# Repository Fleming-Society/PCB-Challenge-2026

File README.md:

# UCL x KCL x Oxford x Imperial x Cambridge x Edinburgh: 2026 PCB Challenge | Sponsored by PCBWay and Jane Street

UCL, KCL and Oxford, Cambridge, Imperial and Edinburgh are proud to present the 2026 PCB Challenge. Many thanks to PCBWay and Jane Street for sponsoring the prizes. 

<p align="center">
  <a href="https://www.janestreet.com">
    <picture>
      <source media="(prefers-color-scheme: dark)" srcset="assets/sponsors/janestreet.png">
      
    </picture>
  </a>
  &nbsp;&nbsp;&nbsp;&nbsp;&nbsp;&nbsp;
  
</p>

If you have any questions please email zceepvb@ucl.ac.uk. Please keep in mind you cannot make a submission/be eligible for the prizes if you do not attend any of the universities organising this event. Within the 7 day period this event is being hosted, any university Engineering society is free to reach out to collaborate at this email address. 

All files are meant for KiCAD v10.0, if you have not updated, you probably should. It is a much better version than KiCAD v9.0 (includes dark mode). 

The event is running from the **12th of October to the 19th of October.**

## Overview

This challenge invites participants to implement the given schematic as a fully wired PCB in the smallest possible size. As an added challenge the purpose of the PCB itself is left ambiguous. You are provided a schematic with all component values and connections intact, and a footprint associated with each schematic symbol. The event runs fully online, and all the necessary information can be found in this GitHub. 

I was inspired to create this challenge by a friend, Taylan Arslan, who gave me what was an essentially impossible challenge to get his PCB to fit within a 40mmx40mm constraint. Despite it being impossible, I learned a lot in those two days trying to accomplish this and the end result is a PCB that I am still very proud of. I hope that participants will also share the same feeling of satisfaction that I got, with the added bonus that this one is not impossible since the smallest possible size is to be determined by one of you. 

From my own experience, no matter how much you may like designing PCBs, ultimately it will become a bit repetitive. Thus to make this challenge more interesting; besides the monetary prize; I also decided to make the purpose of the PCB itself a puzzle to be solved.

## The Challenge

1. **Logic Deduction**: deduce the digital logic function implemented by the provided schematic, purely from the schematic itself (no functional description is given). Deducing this will give you bonus points.
2. **PCB Layout**: design a fully wired, single board PCB implementation of that logic, optimised for the smallest possible board area, within the design constraints below.

This challenge will be running for 7 days, **until the midnight of October 19th. (The end of the 19th)**

Make your **submission** here:
https://forms.cloud.microsoft/Pages/ResponsePage.aspx?id=_oivH5ipW0yTySEKEdmlwtUrHdFLQS5OlbEozvc0DnlUMzJQWkFZVDhVRjZNVTlCQjhHQ0hDSUxSQi4u

Your challenge submission should be a public GitHub repo. In this repo you just need to include the files we need. Your submission for the logic deduction is in the form itself. 

## Design Constraints

The keep out zone of the ESP32 antenna does not have to cover any PCB area, it can be left hanging off the edge of the PCB. Furthermore ignore the datasheets associated with each component in this challenge.

### Board & Layer Stack
- Four layer board (F.Cu / B.Cu + 2 inner layers), 1.6 mm standard FR4 thickness.
- Board outline may be any shape, but must be a single contiguous board (no panelisation or multi-board tricks to reduce measured area).
- Management of the 4 layer stack up (e.g. assignment of signal/power/ground to inner layers) is left entirely to the participant; there is no required or predefined ground/power/signal layer assignment. However, you will be penalised for a stack up that would not actually work. 

### Trace & Clearance Rules
- Minimum trace width: 0.15 mm (6 mil).
- Minimum clearance (trace to trace, trace to pad, trace to via): 0.12 mm (6 mil) (changed from 0.15mm to 0.12mm due to the pads of the flip flop being seperated by 0.12mm).
- Minimum copper to board edge clearance: 0.3 mm.
- These values should be set as the global minimum in KiCad's Clearance rules so DRC enforces them automatically. We will check the DRC ourselves when judging. 

### Via Rules
- Minimum via drill diameter: 0.3 mm.
- Minimum via annular ring: 0.15 mm (i.e. minimum via pad diameter of approximately 0.6 mm).
- Vias in pads are not permitted.

### Footprint Rules
- Only default KiCad footprints, or footprints explicitly provided as part of the challenge, may be used.
- Footprints must not be modified from the library originals (this will be checked via KiCad's "footprint does not match library" DRC warning; note that editing a local copy of the library will not bypass this check, and manual review may also be used).
- All footprints must have correctly defined courtyard layers (F.CrtYd / B.CrtYd), and courtyards must not overlap between components. This is enforced via KiCad's built in "courtyard overlap" DRC check.
- Traces and vias may not be routed underneath IC footprints (i.e. within the courtyard area of any IC); given there is no shield underneath it. This only applies if the IC and trace are on the same layer.

### Silkscreen
- Boards do not need to retain fully legible silkscreen labelling. 

### DRC Pass Criteria
- All submitted boards must pass KiCad's Design Rule Checker to a good degree (Inspect → Design Rules Checker). I understand that the DRC can be quite buggy especially with imported footprints, thus I will be a bit lenient. 
- DRC **warnings** (e.g. minor silkscreen clipping) will not disqualify a board, but excessive or careless warnings may count against a board at the routing quality tie break stage.

#### I am aware that there is an issue with the flip flop footprints and we will ignore any DRC errors associated with them. Just ensure you use a trace width of 0.17mm or less for them. 

### Note on High-Speed & Power Rules
The challenge schematic does include a high speed signal paths (a differential pair requiring a continuous reference plane). It does not however have a significant power delivery requirement (e.g. wide power traces, stitching vias). As such, no specific power plane rules are imposed in this iteration. 

## Judging Criteria

1. **Pass/fail gate**: correct logic deduction and a fully wired, DRC clean board (zero errors) under the given constraints. Boards failing either condition are not eligible for prizes.
2. **Primary ranking metric**: smallest board area (bounding box of the board outline), among all boards that pass the gate above.
3. **Tie breaker**: in the event of a tie, judges will assess routing quality and general layout practice (e.g. via count, trace directness, use of ground fill, silkscreen space, DRC warning count) to determine placement.

## Prizes

- **1st place:** £200
- **2nd place:** £100
- **3rd place:** £50

- **Top 10**: Jane Street Water Bottle
- **Top 65**: Jane Street Tech T-Shirt, 10$ PCBWay Coupon and a PCB Ruler

- All participants who submit a valid entry will receive a certificate of participation, a 10$ coupon on orders above 30$ for PCBWay and a PCB ruler from PCBWay. To be classified as a participant you must actually complete the PCB, this meaning that all the connections have been connected with a trace. Auto trace does not count. 

Expect the results to be announced within a week or two from the end date of the challenge.

## Sponsors

Thank you to our sponsors for making this challenge possible.

<p align="center">
  <a href="https://www.janestreet.com">
    <picture>
      <source media="(prefers-color-scheme: dark)" srcset="assets/sponsors/janestreet.png">
      
    </picture>
  </a>
  &nbsp;&nbsp;&nbsp;&nbsp;&nbsp;&nbsp;
  
</p>

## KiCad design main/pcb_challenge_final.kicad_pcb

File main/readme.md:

## Issues
1. C1-C8, R1, SW1 and SW3 did not have a footprint. 
2. The transistor did not have the correct nets due to being numbered 1, 5 and 6 rather than 1, 2 and 3. 
3. 3v3 instead of +3.3V power net. 
4. Input 1,  Input2, Input 3 and Input 4 rather than b1, b2, b3 and 4.
5. U2 is not a real component.
6. SW2 pins were both GND. This has been resolved.
7. EN on the clock generator should be en. 
8. R24 and R6 do not show a connection to S1, they are supposed to be connected. 

#### Credits to: 
Mickey Techachokwiwat, Andy Gao and Lutfi Cengiz for finding these issues and reporting them to me.

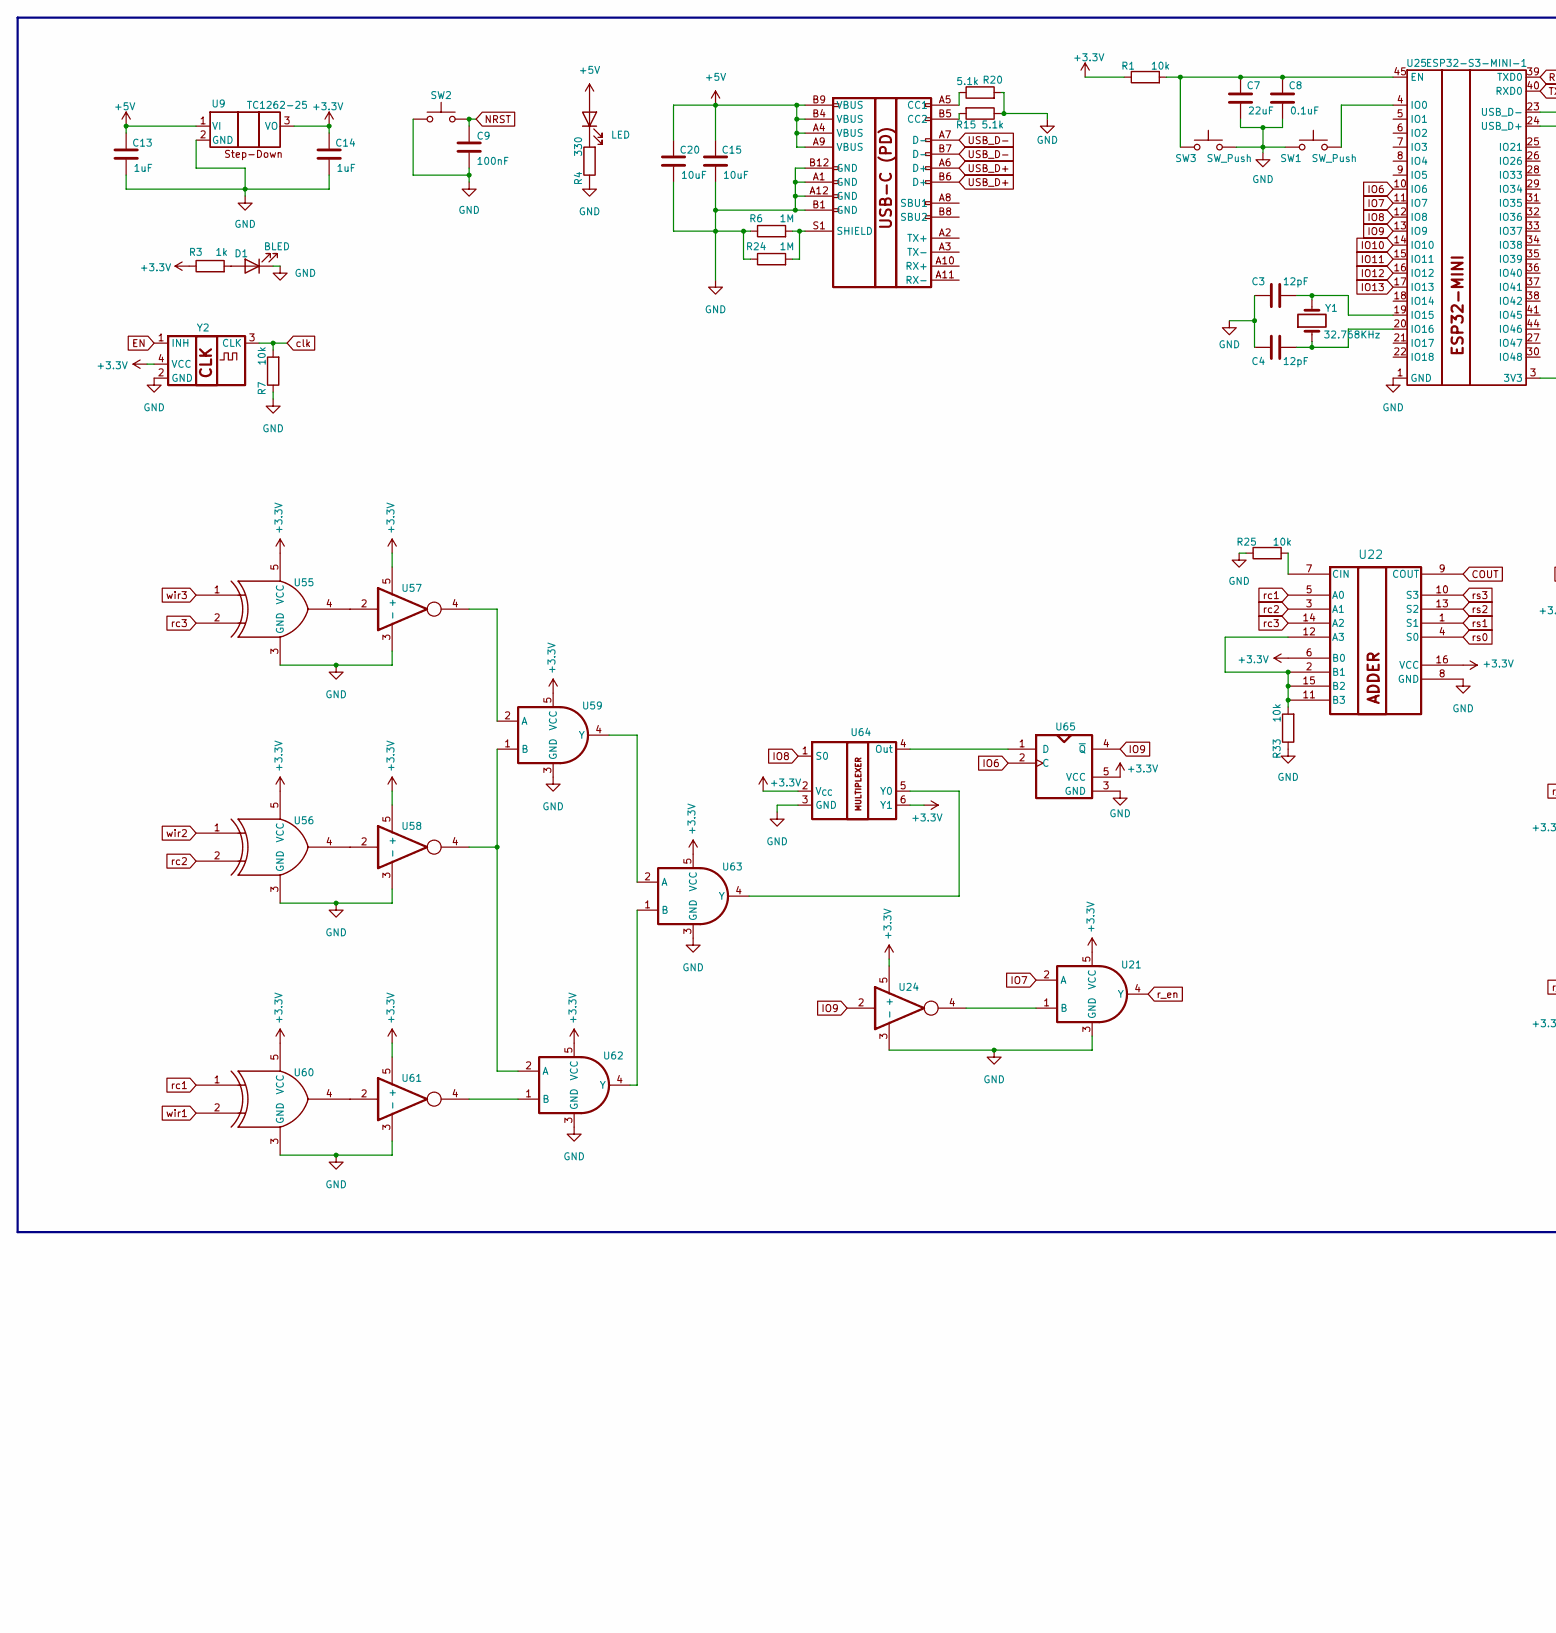
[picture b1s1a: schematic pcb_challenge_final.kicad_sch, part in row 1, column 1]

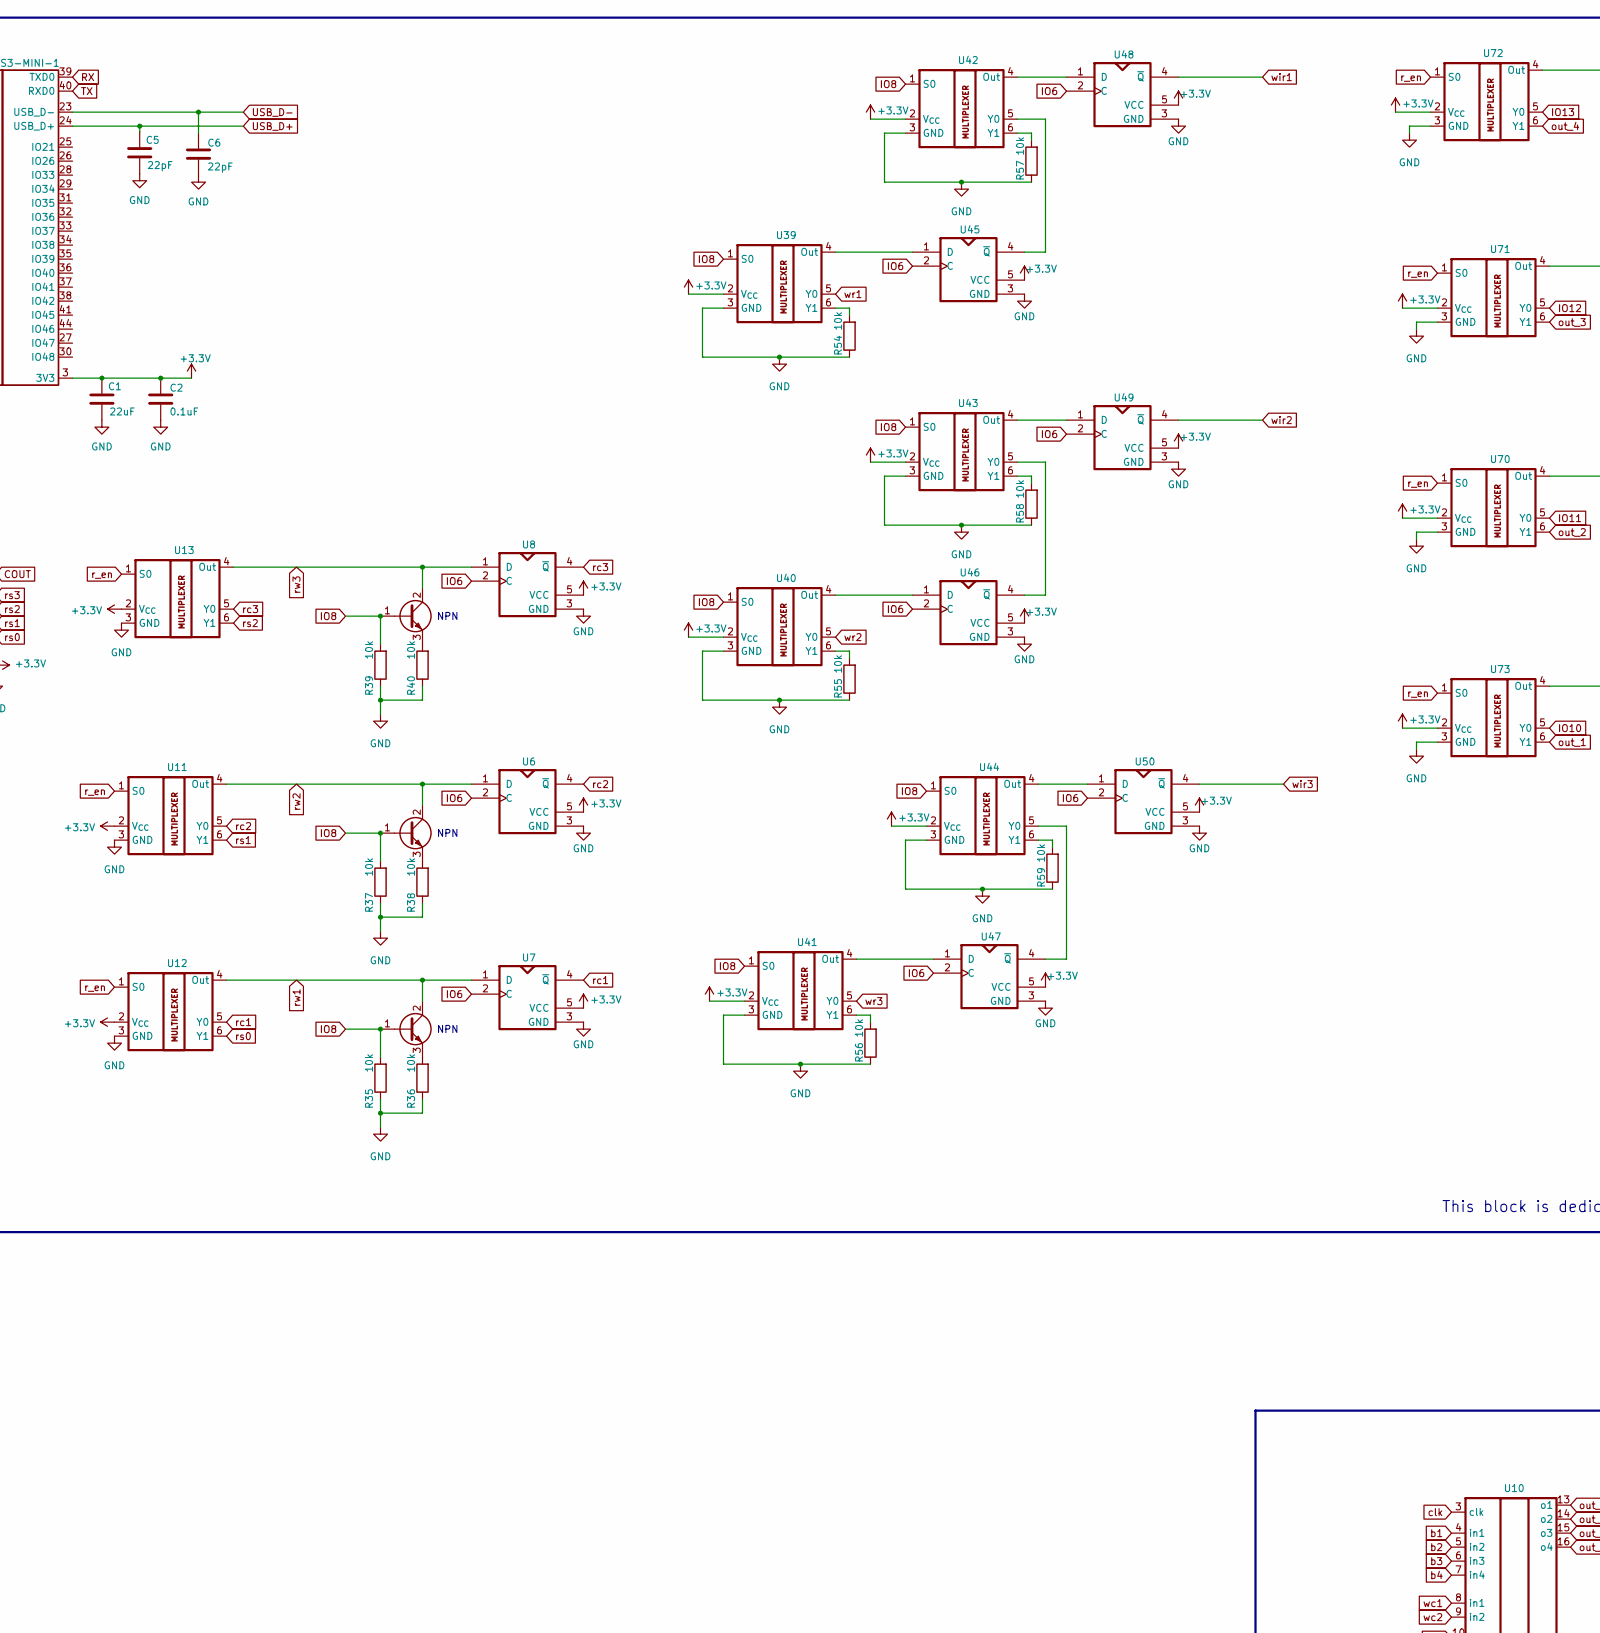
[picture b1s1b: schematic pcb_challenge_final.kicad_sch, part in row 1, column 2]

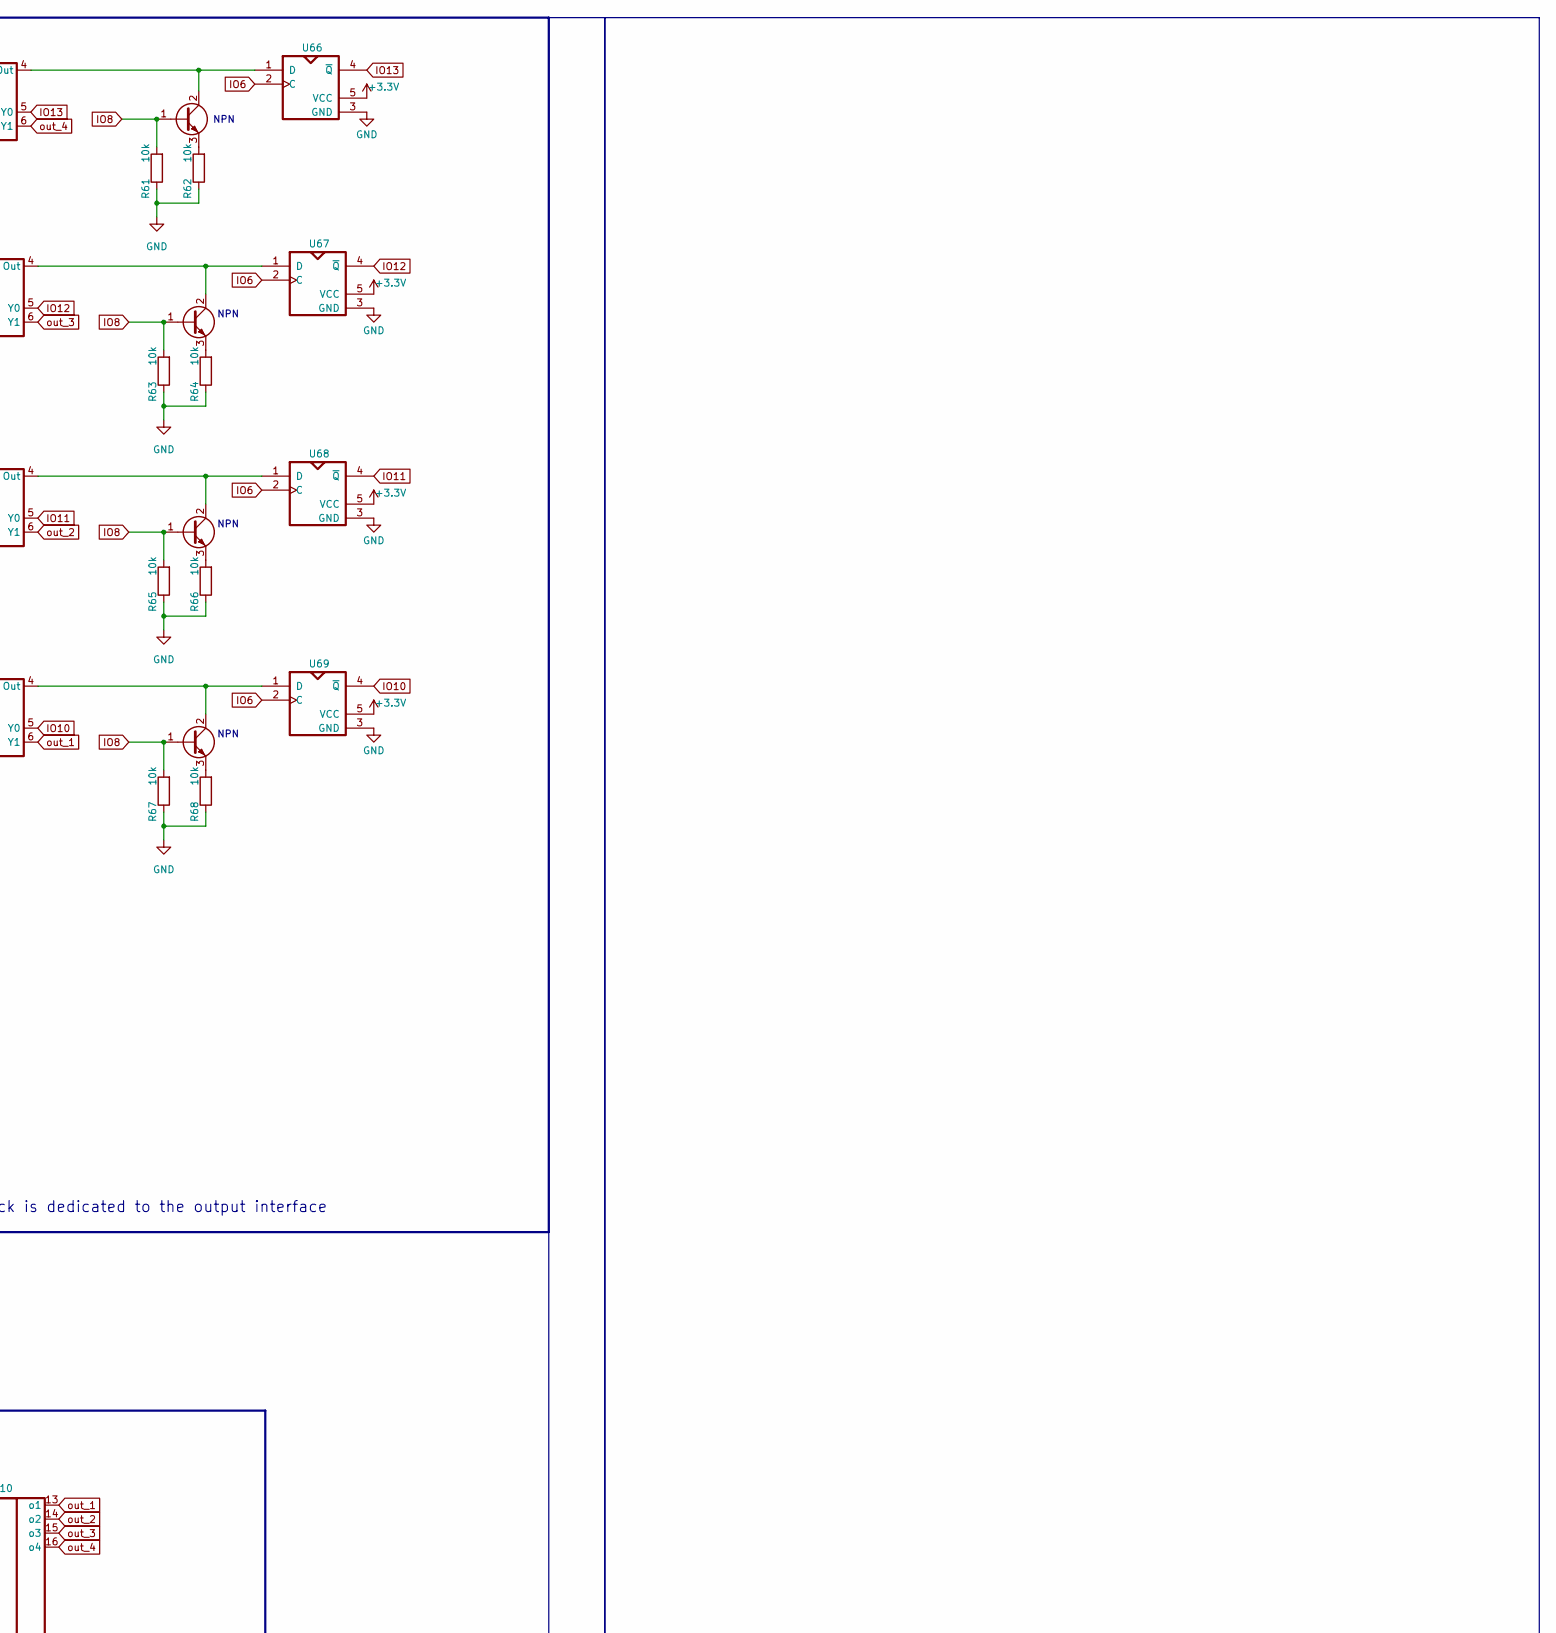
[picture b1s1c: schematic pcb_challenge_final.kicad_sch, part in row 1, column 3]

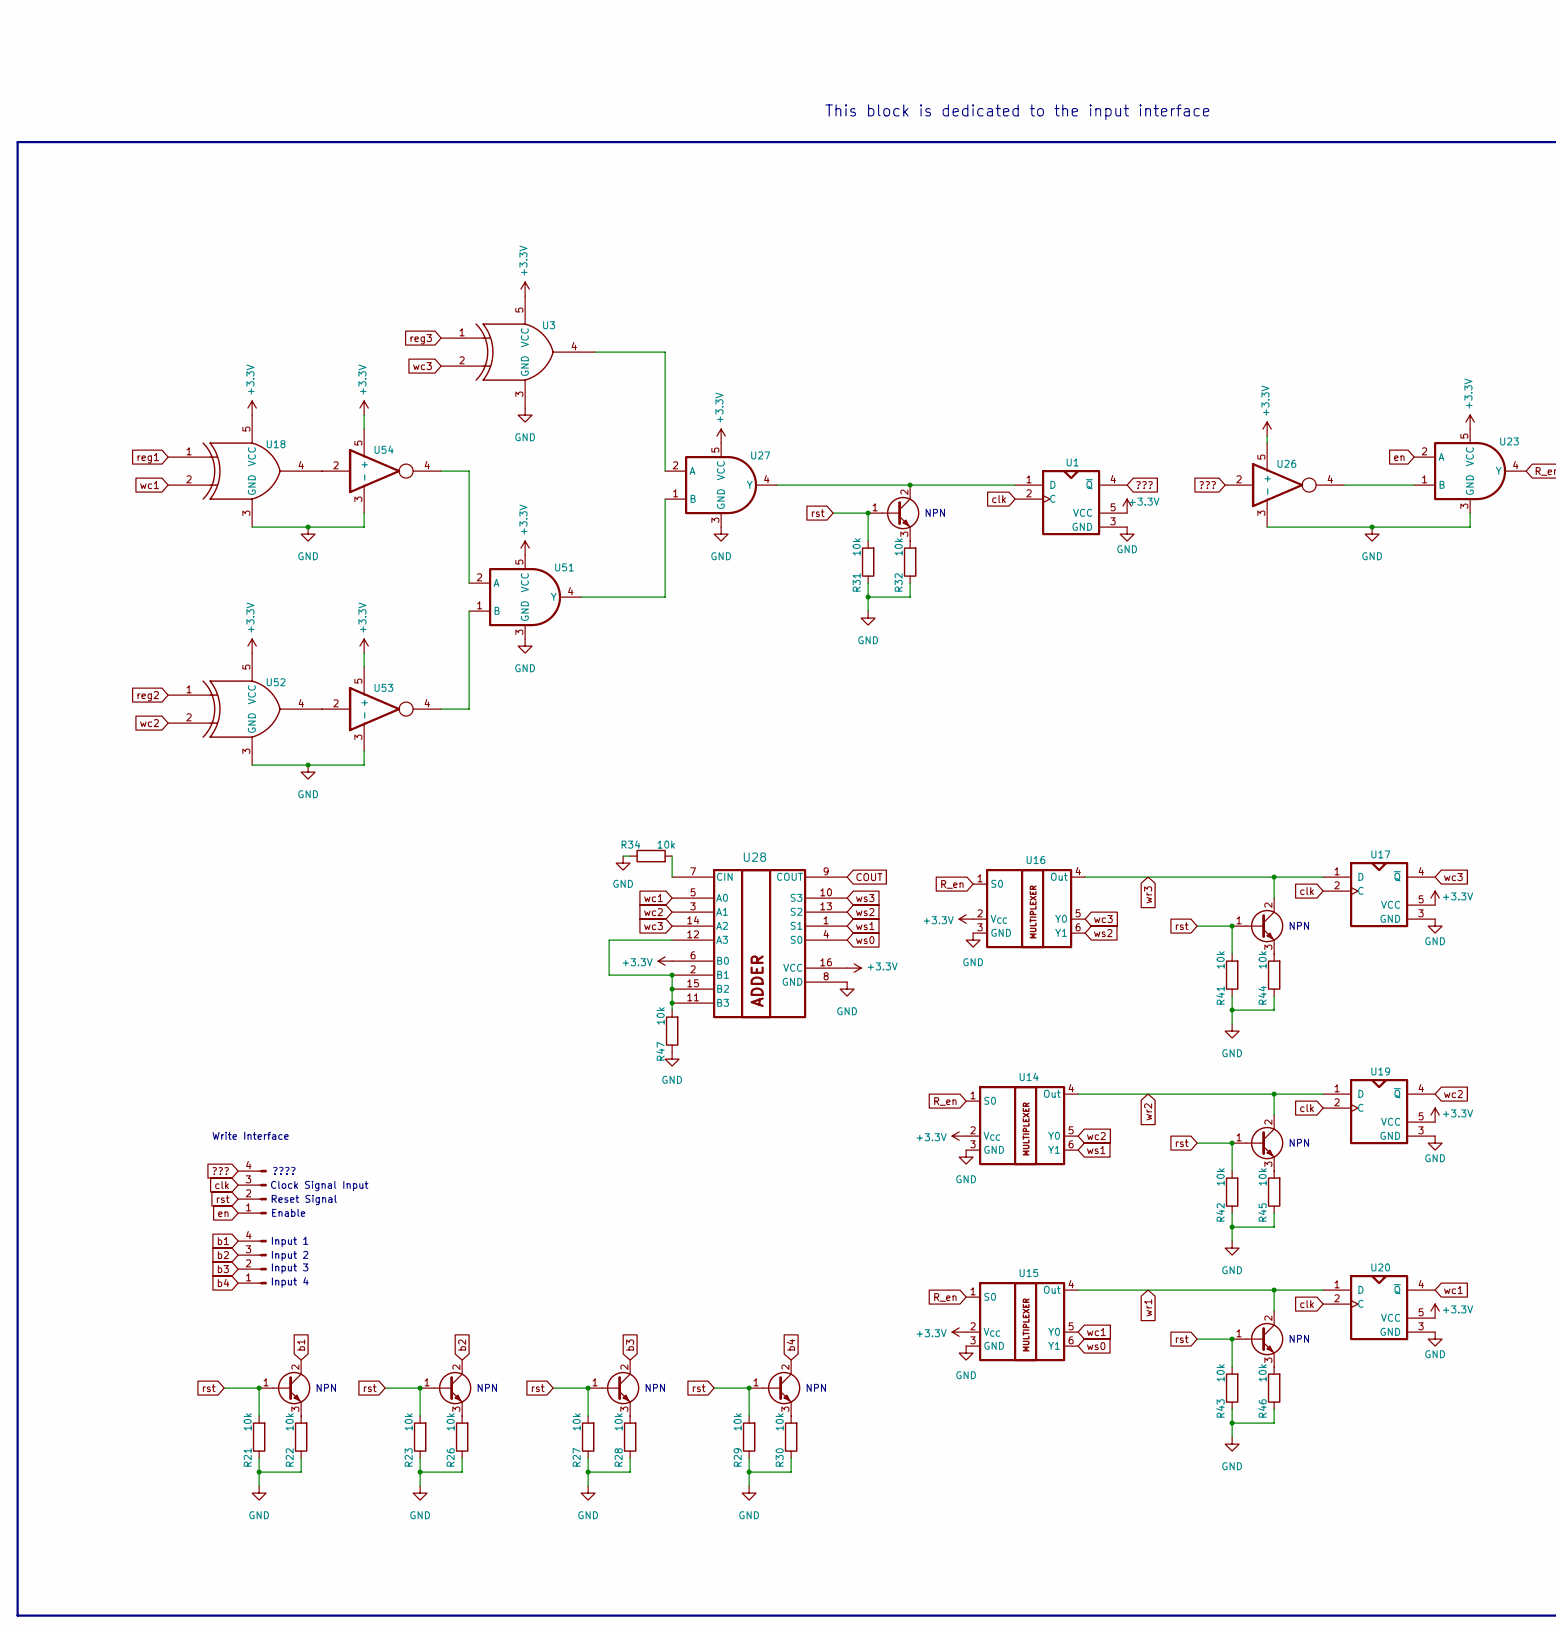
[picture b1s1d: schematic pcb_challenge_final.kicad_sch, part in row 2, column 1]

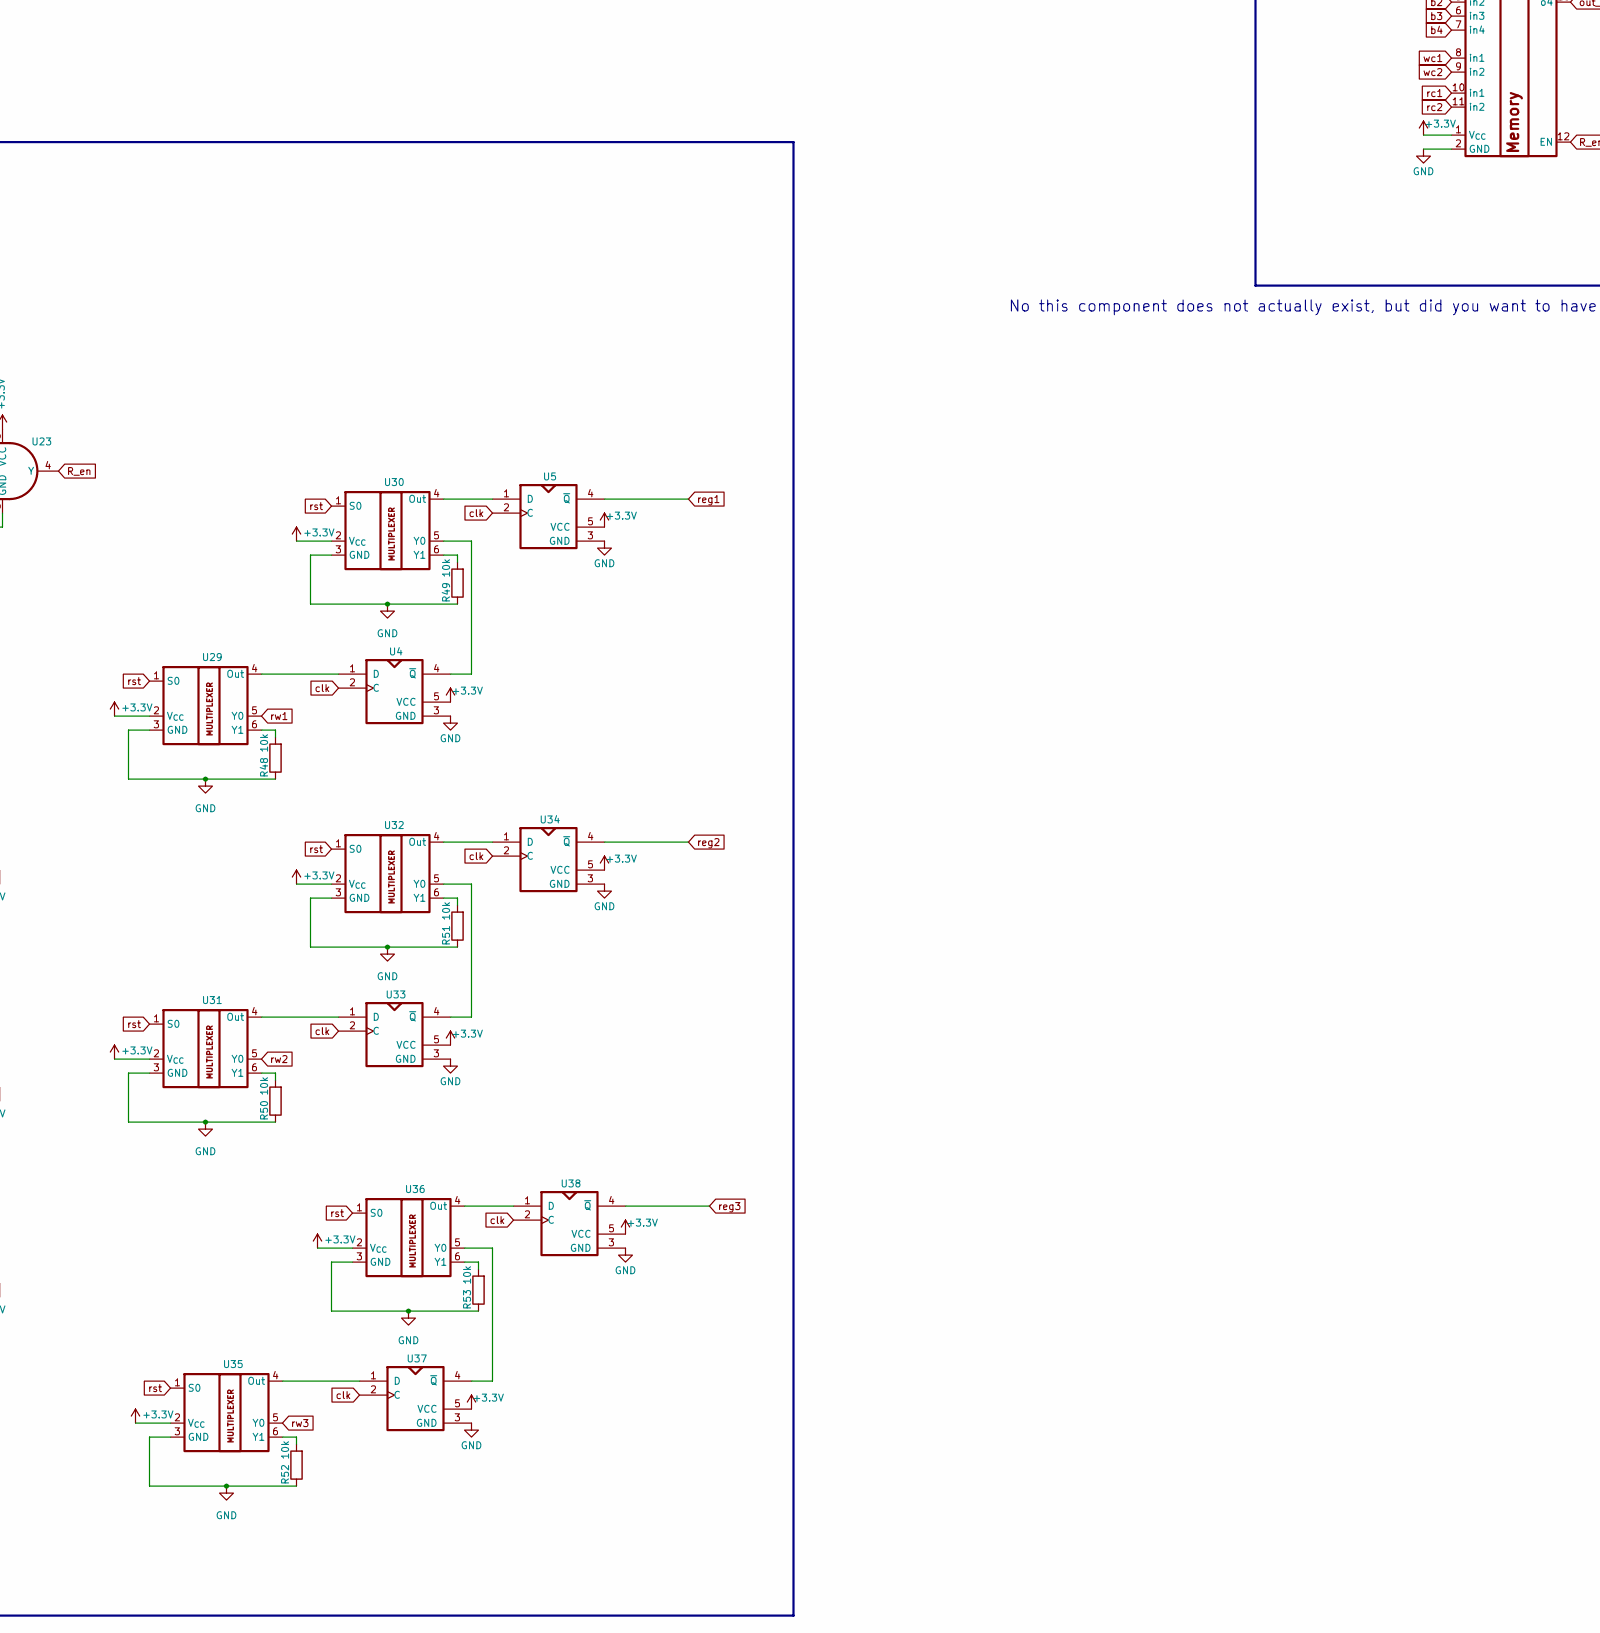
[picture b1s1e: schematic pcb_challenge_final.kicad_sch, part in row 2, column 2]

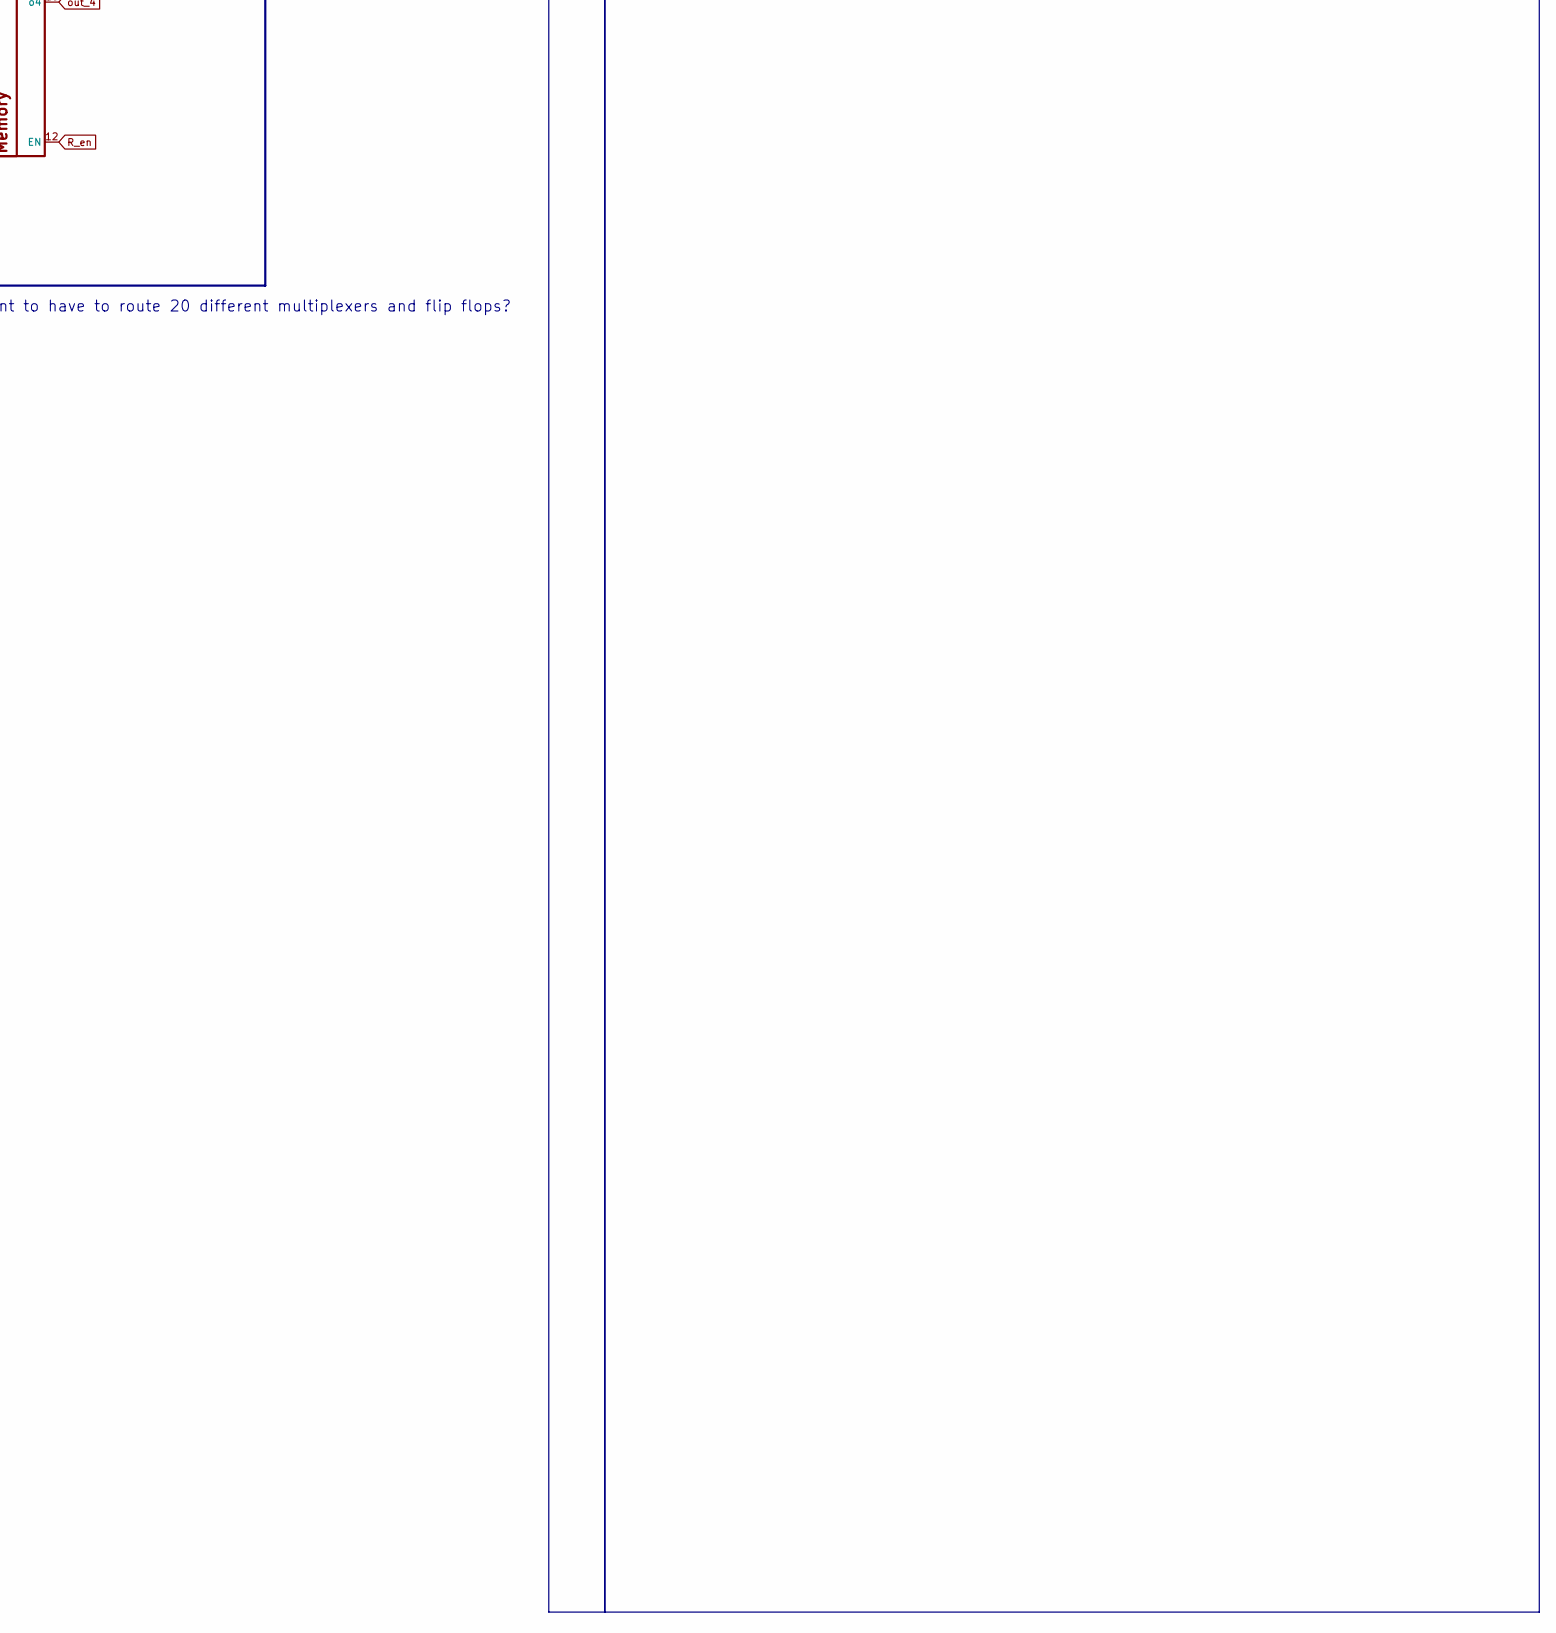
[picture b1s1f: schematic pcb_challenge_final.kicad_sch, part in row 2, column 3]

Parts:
C1, C7: 22uF; C_0201_0603Metric
C2, C8: 0.1uF; C_0201_0603Metric
C3, C4: 12pF; C_0201_0603Metric
C5, C6: 22pF; C_0201_0603Metric
C9: 100nF; C_0402_1005Metric
C13, C14: 1uF; C_0603_1608Metric
C15, C20: 10uF; C_0603_1608Metric
D1: BLED; LED_0603_1608Metric
GREEN_LED1: LED; LED_0603_1608Metric
J3: USB_C_Receptacle_HCTL_HC-TYPE-C-16P-01A
J4, J5: Conn_01x04_Pin; PinHeader_1x04_P2.54mm_Vertical
Q15, Q16, Q17, Q18, Q19, Q20, Q21, Q22, Q23, Q24, Q25, Q26, Q27, Q28, Q29: Q_Dual_NPN_PNP_B1E2B2C2E1C1; SOT-1123
R1: 10k; C_0402_1005Metric
R3: 1k; C_0603_1608Metric
R4: 330; C_0603_1608Metric
R6, R24: 1M; C_0603_1608Metric
R7, R21, R22, R23, R25, R26, R27, R28, R29, R30, R31, R32, R33, R34, R35, R36, R37, R38, R39, R40, R41, R42, R43, R44, R45, R46, R47, R48, R49, R50, R51, R52, R53, R54, R55, R56, R57, R58, R59, R61, R62, R63, R64, R65, R66, R67, R68: 10k; C_0603_1608Metric
R15, R20: 5.1k; R_0603_1608Metric_Pad0.98x0.95mm_HandSolder
SW1, SW3: SW_Push; SW_DIP_SPSTx01_Slide_6.7x4.1mm_W8.61mm_P2.54mm_LowProfile
SW2: SW_MEC_5G; SW_SPST_CK_RS282G05A3
U1, U4, U5, U6, U7, U8, U17, U19, U20, U33, U34, U37, U38, U45, U46, U47, U48, U49, U50, U65, U66, U67, U68, U69: 74AUP1G80; XSON6_SOT1115_NEX
U3, U18, U52, U55, U56, U60: 74AHC1G86; SC-74A-5_1.55x2.9mm_P0.95mm
U9: TC1262-25; SOT-223_3MC_MCH
U10: NMUX1308BQ; SO-16_3.9x9.9mm_P1.27mm
U11, U12, U13, U14, U15, U16, U29, U30, U31, U32, U35, U36, U39, U40, U41, U42, U43, U44, U64, U70, U71, U72, U73: NMUX1308BQ; SOT-363_SC-70-6
U21, U23, U27, U51, U59, U62, U63: 74LV1T08GV; SC-74A-5_1.55x2.9mm_P0.95mm
U22, U28: CD74HC283M96; D16
U24, U26, U53, U54, U57, U58, U61: 74LVC1GU04DRL; SOT-553
U25: ESP32-S3-MINI-1; ESP32-S2-MINI-1
Y1: 32.768KHz; Crystal_SMD_Abracon_ABM7-2Pin_6.0x3.5mm
Y2: KC2520Z; Oscillator_SMD_Kyocera_KC2520Z-4Pin_2.5x2.0mm

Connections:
+3.3V: C1.1, C2.1, C14.1, R1.1, R3.1, U1.5 (VCC), U3.5 (VCC), U4.5 (VCC), U5.5 (VCC), U6.5 (VCC), U7.5 (VCC), U8.5 (VCC), U9.3 (VO), U10.1 (V_{CC}), U11.2 (V_{CC}), U12.2 (V_{CC}), U13.2 (V_{CC}), U14.2 (V_{CC}), U15.2 (V_{CC}), U16.2 (V_{CC}), U17.5 (VCC), U18.5 (VCC), U19.5 (VCC), U20.5 (VCC), U21.5 (VCC), U22.6 (B0), U22.16 (VCC), U23.5 (VCC), U24.5 (+), U25.3 (3V3), U26.5 (+), U27.5 (VCC), U28.6 (B0), U28.16 (VCC), U29.2 (V_{CC}), U30.2 (V_{CC}), U31.2 (V_{CC}), U32.2 (V_{CC}), U33.5 (VCC), U34.5 (VCC), U35.2 (V_{CC}), U36.2 (V_{CC}), U37.5 (VCC), U38.5 (VCC), U39.2 (V_{CC}), U40.2 (V_{CC}), U41.2 (V_{CC}), U42.2 (V_{CC}), U43.2 (V_{CC}), U44.2 (V_{CC}), U45.5 (VCC), U46.5 (VCC), U47.5 (VCC), U48.5 (VCC), U49.5 (VCC), U50.5 (VCC), U51.5 (VCC), U52.5 (VCC), U53.5 (+), U54.5 (+), U55.5 (VCC), U56.5 (VCC), U57.5 (+), U58.5 (+), U59.5 (VCC), U60.5 (VCC), U61.5 (+), U62.5 (VCC), U63.5 (VCC), U64.2 (V_{CC}), U64.6 (Y1), U65.5 (VCC), U66.5 (VCC), U67.5 (VCC), U68.5 (VCC), U69.5 (VCC), U70.2 (V_{CC}), U71.2 (V_{CC}), U72.2 (V_{CC}), U73.2 (V_{CC}), Y2.4 (VCC)
+5V: C13.1, C15.1, C20.1, GREEN_LED1.2 (A), J3.A4 (VBUS), J3.A9 (VBUS), J3.B4 (VBUS), J3.B9 (VBUS), U9.1 (VI)
???: J5.4, U1.4 (~Q), U26.2
COUT: U22.9 (COUT), U28.9 (COUT)
EN: Y2.1 (INH)
IO6: U6.2 (C), U7.2 (C), U8.2 (C), U25.10 (IO6), U45.2 (C), U46.2 (C), U47.2 (C), U48.2 (C), U49.2 (C), U50.2 (C), U65.2 (C), U66.2 (C), U67.2 (C), U68.2 (C), U69.2 (C)
IO7: U21.2 (A), U25.11 (IO7)
IO8: Q18.1 (B1), Q19.1 (B1), Q20.1 (B1), Q24.1 (B1), Q25.1 (B1), Q26.1 (B1), Q27.1 (B1), R35.2, R37.2, R39.2, R61.2, R63.2, R65.2, R67.2, U25.12 (IO8), U39.1 (S0), U40.1 (S0), U41.1 (S0), U42.1 (S0), U43.1 (S0), U44.1 (S0), U64.1 (S0)
IO9: U24.2, U25.13 (IO9), U65.4 (~Q)
IO10: U25.14 (IO10), U69.4 (~Q), U73.5 (Y0)
IO11: U25.15 (IO11), U68.4 (~Q), U70.5 (Y0)
IO12: U25.16 (IO12), U67.4 (~Q), U71.5 (Y0)
IO13: U25.17 (IO13), U66.4 (~Q), U72.5 (Y0)
unnamed: D1.2 (A), R3.2
unnamed: GREEN_LED1.1 (K), R4.2
unnamed: J3.A5 (CC1), R20.1
unnamed: J3.B5 (CC2), R15.2
unnamed: J3.S1 (SHIELD), R6.2, R24.2
unnamed: Q15.3 (E1), R30.2
unnamed: Q16.2 (C1), U1.1 (D), U27.4 (Y)
unnamed: Q16.3 (E1), R32.2
unnamed: Q17.3 (E1), R28.2
unnamed: Q18.3 (E1), R40.2
unnamed: Q19.3 (E1), R38.2
unnamed: Q20.3 (E1), R36.2
unnamed: Q21.3 (E1), R44.2
unnamed: Q22.3 (E1), R45.2
unnamed: Q23.3 (E1), R46.2
unnamed: Q24.2 (C1), U66.1 (D), U72.4 (Out)
unnamed: Q24.3 (E1), R62.2
unnamed: Q25.2 (C1), U67.1 (D), U71.4 (Out)
unnamed: Q25.3 (E1), R64.2
unnamed: Q26.2 (C1), U68.1 (D), U70.4 (Out)
unnamed: Q26.3 (E1), R66.2
unnamed: Q27.2 (C1), U69.1 (D), U73.4 (Out)
unnamed: Q27.3 (E1), R68.2
unnamed: Q28.3 (E1), R26.2
unnamed: Q29.3 (E1), R22.2
unnamed: U18.4, U54.2
unnamed: U21.1 (B), U24.4
unnamed: R33.2, U22.2 (B1), U22.11 (B3), U22.12 (A3), U22.15 (B2)
unnamed: R25.2, U22.7 (CIN)
unnamed: U23.1 (B), U26.4
unnamed: C7.1, C8.1, R1.2, SW3.1, U25.45 (EN)
unnamed: U25.2 (GND), U25.42 (GND), U25.43 (GND), U25.46 (GND), U25.47 (GND), U25.48 (GND), U25.49 (GND), U25.50 (GND), U25.51 (GND), U25.52 (GND), U25.53 (GND), U25.54 (GND), U25.55 (GND), U25.56 (GND), U25.57 (GND), U25.58 (GND), U25.59 (GND), U25.60 (GND), U25.61 (GND), U25.62 (GND), U25.63 (GND), U25.64 (GND), U25.65 (GND)
unnamed: SW1.2, U25.4 (IO0)
unnamed: C3.2, U25.19 (IO15), Y1.2
unnamed: C4.2, U25.20 (IO16), Y1.1
unnamed: U3.4, U27.2 (A)
unnamed: U27.1 (B), U51.4 (Y)
unnamed: R47.2, U28.2 (B1), U28.11 (B3), U28.12 (A3), U28.15 (B2)
unnamed: R34.2, U28.7 (CIN)
unnamed: U4.1 (D), U29.4 (Out)
unnamed: R48.2, U29.6 (Y1)
unnamed: U5.1 (D), U30.4 (Out)
unnamed: U4.4 (~Q), U30.5 (Y0)
unnamed: R49.2, U30.6 (Y1)
unnamed: U31.4 (Out), U33.1 (D)
unnamed: R50.2, U31.6 (Y1)
unnamed: U32.4 (Out), U34.1 (D)
unnamed: U32.5 (Y0), U33.4 (~Q)
unnamed: R51.2, U32.6 (Y1)
unnamed: U35.4 (Out), U37.1 (D)
unnamed: R52.2, U35.6 (Y1)
unnamed: U36.4 (Out), U38.1 (D)
unnamed: U36.5 (Y0), U37.4 (~Q)
unnamed: R53.2, U36.6 (Y1)
unnamed: U39.4 (Out), U45.1 (D)
unnamed: R54.2, U39.6 (Y1)
unnamed: U40.4 (Out), U46.1 (D)
unnamed: R55.2, U40.6 (Y1)
unnamed: U41.4 (Out), U47.1 (D)
unnamed: R56.2, U41.6 (Y1)
unnamed: U42.4 (Out), U48.1 (D)
unnamed: U42.5 (Y0), U45.4 (~Q)
unnamed: R57.2, U42.6 (Y1)
unnamed: U43.4 (Out), U49.1 (D)
unnamed: U43.5 (Y0), U46.4 (~Q)
unnamed: R58.2, U43.6 (Y1)
unnamed: U44.4 (Out), U50.1 (D)
unnamed: U44.5 (Y0), U47.4 (~Q)
unnamed: R59.2, U44.6 (Y1)
unnamed: U51.2 (A), U54.4
unnamed: U51.1 (B), U53.4
unnamed: U52.4, U53.2
unnamed: U55.4, U57.2
unnamed: U56.4, U58.2
unnamed: U57.4, U59.2 (A)
unnamed: U58.4, U59.1 (B), U62.2 (A)
unnamed: U59.4 (Y), U63.2 (A)
unnamed: U60.4, U61.2
unnamed: U61.4, U62.1 (B)
unnamed: U62.4 (Y), U63.1 (B)
unnamed: U63.4 (Y), U64.5 (Y0)
unnamed: U64.4 (Out), U65.1 (D)
RX: U25.39 (TXD0)
R_en: U10.12 (EN), U14.1 (S0), U15.1 (S0), U16.1 (S0), U23.4 (Y)
TX: U25.40 (RXD0)
USB_D+: C5.1, J3.A6 (D+), J3.B6 (D+), U25.24 (USB_D+)
USB_D-: C6.1, J3.A7 (D-), J3.B7 (D-), U25.23 (USB_D-)
b1: J4.4, Q29.2 (C1), U10.4 (in1)
b2: J4.3, Q28.2 (C1), U10.5 (in2)
b3: J4.2, Q17.2 (C1), U10.6 (in3)
b4: J4.1, Q15.2 (C1), U10.7 (in4)
clk: J5.3, R7.2, U1.2 (C), U4.2 (C), U5.2 (C), U10.3 (clk), U17.2 (C), U19.2 (C), U20.2 (C), U33.2 (C), U34.2 (C), U37.2 (C), U38.2 (C), Y2.3 (CLK)
en: J5.1, U23.2 (A)
out_1: U10.13 (o1), U73.6 (Y1)
out_2: U10.14 (o2), U70.6 (Y1)
out_3: U10.15 (o3), U71.6 (Y1)
out_4: U10.16 (o4), U72.6 (Y1)
r_en: U11.1 (S0), U12.1 (S0), U13.1 (S0), U21.4 (Y), U70.1 (S0), U71.1 (S0), U72.1 (S0), U73.1 (S0)
rc1: U7.4 (~Q), U10.10 (in1), U12.5 (Y0), U22.5 (A0), U60.1
rc2: U6.4 (~Q), U10.11 (in2), U11.5 (Y0), U22.3 (A1), U56.2
rc3: U8.4 (~Q), U13.5 (Y0), U22.14 (A2), U55.2
reg1: U5.4 (~Q), U18.1
reg2: U34.4 (~Q), U52.1
reg3: U3.1, U38.4 (~Q)
rs0: U12.6 (Y1), U22.4 (S0)
rs1: U11.6 (Y1), U22.1 (S1)
rs2: U13.6 (Y1), U22.13 (S2)
rs3: U22.10 (S3)
rw1: Q20.2 (C1), U7.1 (D), U12.4 (Out), U29.5 (Y0)
rw2: Q19.2 (C1), U6.1 (D), U11.4 (Out), U31.5 (Y0)
rw3: Q18.2 (C1), U8.1 (D), U13.4 (Out), U35.5 (Y0)
wc1: U10.8 (in1), U15.5 (Y0), U18.2, U20.4 (~Q), U28.5 (A0)
wc2: U10.9 (in2), U14.5 (Y0), U19.4 (~Q), U28.3 (A1), U52.2
wc3: U3.2, U16.5 (Y0), U17.4 (~Q), U28.14 (A2)
wir1: U48.4 (~Q), U60.2
wir2: U49.4 (~Q), U56.1
wir3: U50.4 (~Q), U55.1
wr1: Q23.2 (C1), U15.4 (Out), U20.1 (D), U39.5 (Y0)
wr2: Q22.2 (C1), U14.4 (Out), U19.1 (D), U40.5 (Y0)
wr3: Q21.2 (C1), U16.4 (Out), U17.1 (D), U41.5 (Y0)
ws0: U15.6 (Y1), U28.4 (S0)
ws1: U14.6 (Y1), U28.1 (S1)
ws2: U16.6 (Y1), U28.13 (S2)
ws3: U28.10 (S3)

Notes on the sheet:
NPN
Reset Signal
This block is dedicated to the input interface
Clock Signal Input
Enable
Input 2
Input 3
No this component does not actually exist, but did you want to have to route 20 different multiplexers and flip flops?
????
Input 1
Input 4
Write Interface
This block is dedicated to the output interface

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
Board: 2 copper layers, 164 parts (0 on the bottom side), 134 nets, no tracks yet.
